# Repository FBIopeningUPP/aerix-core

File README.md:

# AERIX Core

A compact STM32H7 flight controller module.

## Hardware

- STM32H743IIKx
- IIM-42653, ICM-45686, and BMI088 IMUs
- BMP390 and ICP-20100 barometers
- W25Q128JV SPI flash
- microSD card
- Two CAN transceivers
- Buck converter and three 3.3 V LDOs
- SWD and two status LEDs
- Two board-to-board connectors

This board is still being tested and is not ready for flight.

## Board views

## Bring-up

1. Open the [KiCad project](hardware/core/core.kicad_pro).
2. Run ERC and DRC.
3. Check the board for shorts.
4. Power it from a current-limited 3.3 V supply.
5. Connect `VTREF`, `GND`, `SWDIO`, `SWCLK`, and `RESET`.
6. Flash the LED test from the [firmware guide](firmware/README.md).
7. Test storage, sensors, and CAN separately.

## Files

- [Main schematic](hardware/core/core.kicad_sch)
- [MCU schematic](hardware/core/mcu.kicad_sch)
- [Sensor schematic](hardware/core/sensor.kicad_sch)
- [Power schematic](hardware/core/power.kicad_sch)
- [PCB layout](hardware/core/core.kicad_pcb)
- [Symbols, footprints, and 3D models](lib/)
- [Production files](hardware/core/production/)

## Production

- [Bill of materials](hardware/core/production/bom.csv)
- [Component positions](hardware/core/production/positions.csv)
- [Designators](hardware/core/production/designators.csv)
- [IPC netlist](hardware/core/production/netlist.ipc)

The BOM contains 25 line items and 91 parts.

| Designator | Footprint | Qty | Value | Source |
| --- | --- | ---: | --- | --- |
| C1, C2-C15, C20, C22, C24, C27, C28, C30, C31, C33-C38, C40, C41, C43, C44, C46-C48 | 0201 | 35 | 100nF | [LCSC search](https://www.lcsc.com/search?q=0201%20100nF) |
| C16-C18 | 0201 | 3 | 4.7uF | [LCSC search](https://www.lcsc.com/search?q=0201%204.7uF) |
| C19, C21, C23, C51-C56 | 0402 | 9 | 1uF | [LCSC search](https://www.lcsc.com/search?q=0402%201uF) |
| C25, C26, C29, C32 | 0402 | 4 | 2.2uF | [LCSC search](https://www.lcsc.com/search?q=0402%202.2uF) |
| C42, C45 | 0402 | 2 | 4.7uF | [LCSC search](https://www.lcsc.com/search?q=0402%204.7uF) |
| C49 | 0603 | 1 | 10uF | [LCSC search](https://www.lcsc.com/search?q=0603%2010uF) |
| C50 | 0603 | 1 | 22uF | [LCSC search](https://www.lcsc.com/search?q=0603%2022uF) |
| CARD1 | TF-SMD_TF-021B-H265 | 1 | TF-021B-H265 | [C498185](https://www.lcsc.com/product-detail/C498185.html) |
| CN1, CN2 | CONN-SMD_DF40C-80DS-0.4V-51 | 2 | DF40C-80DS-0.4V | [C312960](https://www.lcsc.com/product-detail/C312960.html) |
| FB1-FB3 | 0603 | 3 | 600R | [LCSC search](https://www.lcsc.com/search?q=0603%20600R%20ferrite%20bead) |
| LED1, LED2 | 0402 | 2 | LED | [LCSC search](https://www.lcsc.com/search?q=0402%20LED) |
| R1-R7 | 0201 | 7 | 10k | [LCSC search](https://www.lcsc.com/search?q=0201%2010k) |
| R8-R12 | 0201 | 5 | 47k | [LCSC search](https://www.lcsc.com/search?q=0201%2047k) |
| R13, R14 | 0201 | 2 | 1k | [LCSC search](https://www.lcsc.com/search?q=0201%201k) |
| U1 | UFBGA-201 | 1 | STM32H743IIKx | [LCSC search](https://www.lcsc.com/search?q=STM32H743IIKx) |
| U9, U10 | TDFN-8 | 2 | TCAN1044AVDRBRQ1 | [C3234119](https://www.lcsc.com/product-detail/C3234119.html) |
| U11-U13 | X2SON-4 | 3 | TPS7A2033PDQNR | [C2871641](https://www.lcsc.com/product-detail/C2871641.html) |
| U14 | USIP-10 | 1 | TPSM82822SILR | [C5219367](https://www.lcsc.com/product-detail/C5219367.html) |
| U2 | LGA-14 | 1 | IIM-42653 | [C30724128](https://www.lcsc.com/product-detail/C30724128.html) |
| U3 | LGA-14 | 1 | ICM-45686 | [C22459454](https://www.lcsc.com/product-detail/C22459454.html) |
| U4 | LGA-16 | 1 | BMI088 | [C194919](https://www.lcsc.com/product-detail/C194919.html) |
| U5 | LGA-10 | 1 | BMP390 | [C5124834](https://www.lcsc.com/product-detail/C5124834.html) |
| U6 | LGA-10 | 1 | ICP-20100 | [C5343527](https://www.lcsc.com/product-detail/C5343527.html) |
| U7 | WSON-8 | 1 | W25Q128JVE | [LCSC search](https://www.lcsc.com/search?q=W25Q128JVE) |
| X1 | 3.2 × 2.5 mm crystal | 1 | ABM8W-16.0000MHZ-8-D1X-T3 | [C193746](https://www.lcsc.com/product-detail/C193746.html) |

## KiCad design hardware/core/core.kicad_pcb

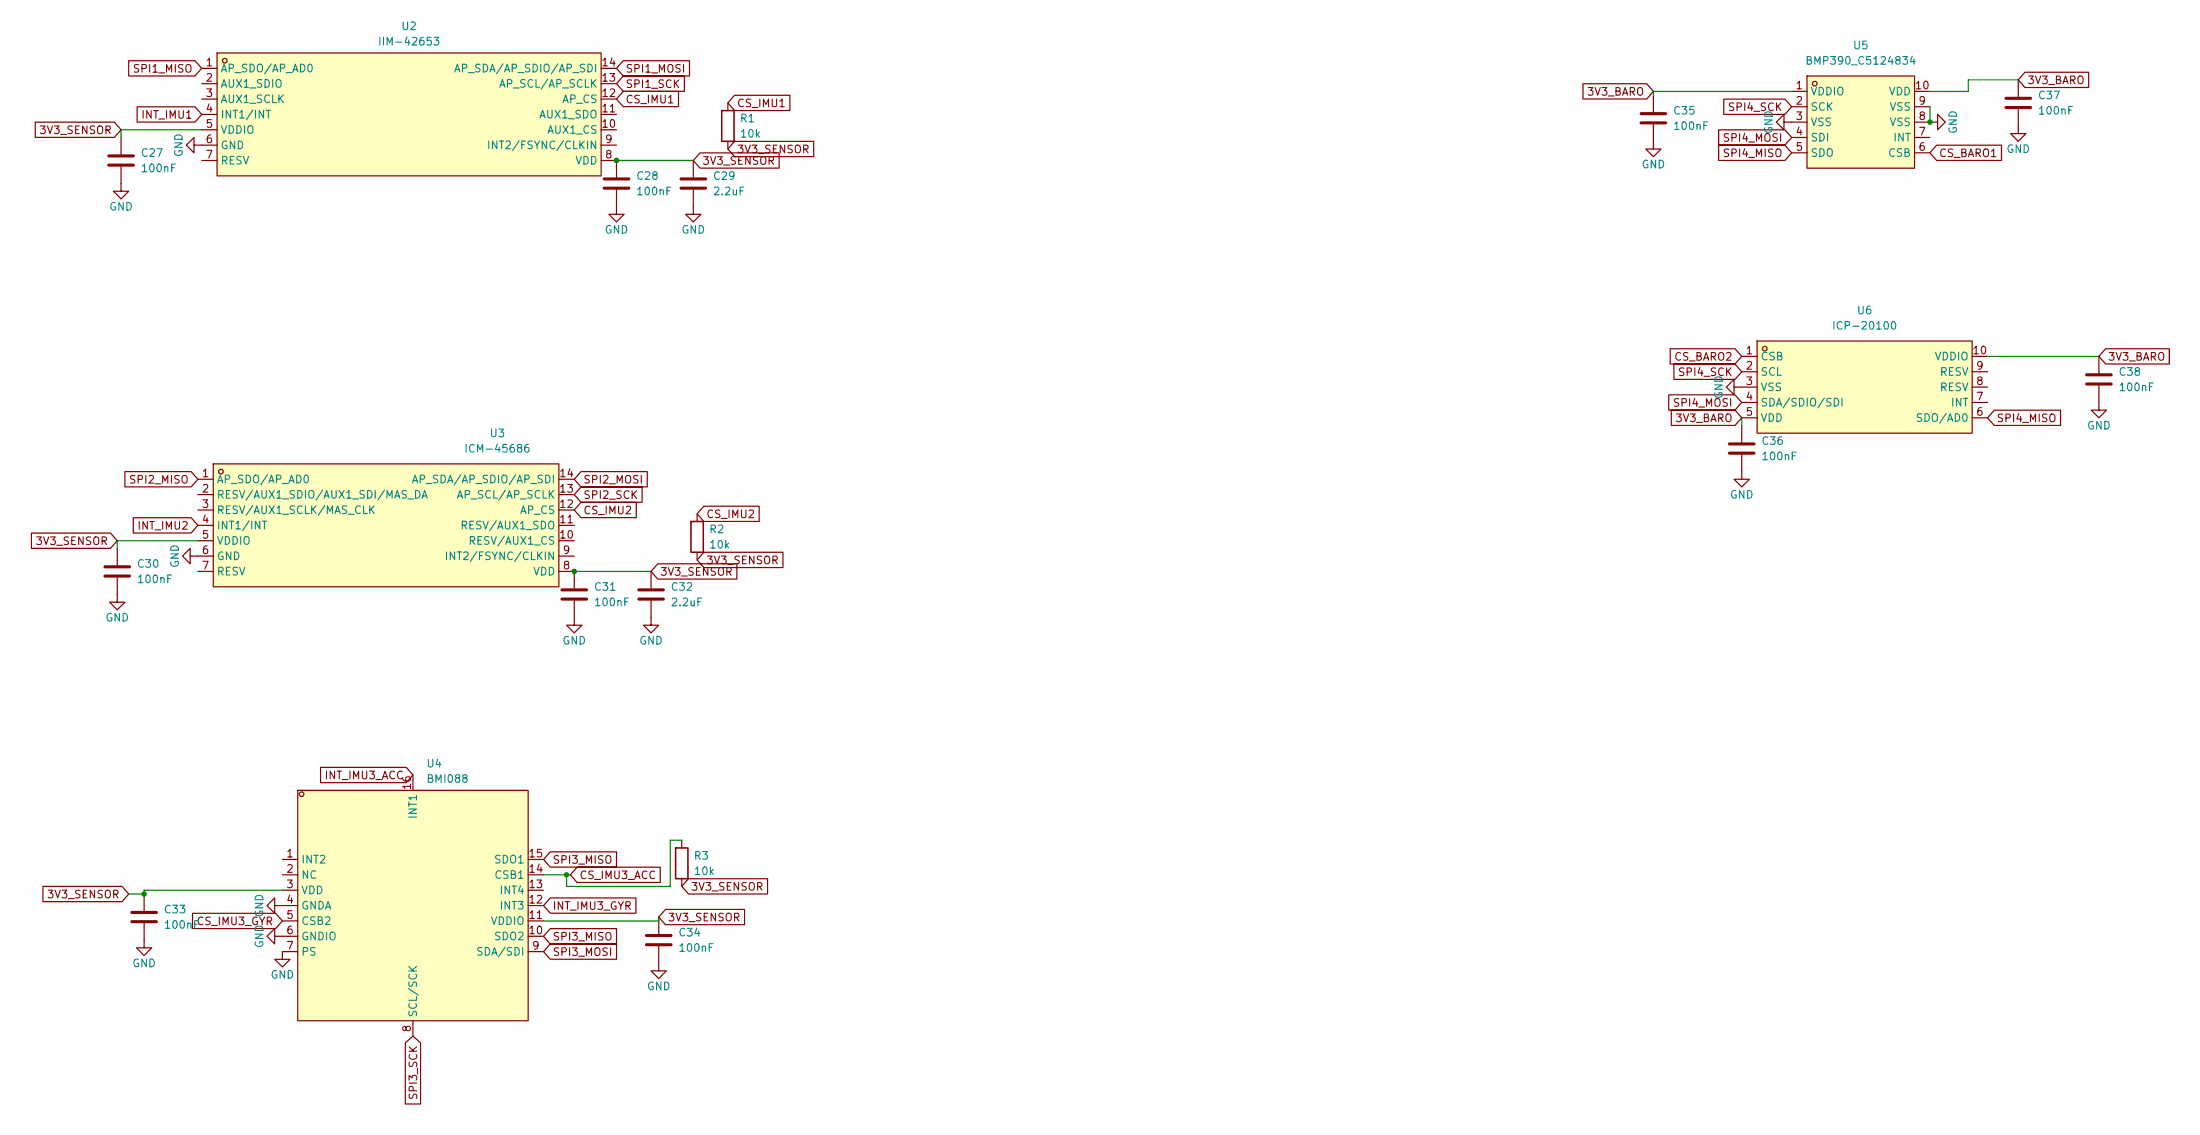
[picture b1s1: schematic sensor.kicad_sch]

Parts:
C27, C28, C30, C31, C33, C34, C35, C36, C37, C38: 100nF; C_0201_0603Metric
C29, C32: 2.2uF; C_0402_1005Metric
R1, R2, R3: 10k; R_0201_0603Metric
U2: IIM-42653; LGA-14_L3.0-W2.5-P0.50-TL; MPN IIM-42653; LCSC Part C30724128
U3: ICM-45686; LGA-14_L3.0-W2.5-P0.50-TL; MPN ICM-45686; LCSC Part C22459454
U4: BMI088; LGA-16_L4.5-W3.0-P0.50-BL; MPN BMI088; LCSC Part C194919
U5: BMP390_C5124834; LGA-10_L2.0-W2.0-P0.50-BL; MPN BMP390; LCSC Part C5124834
U6: ICP-20100; LGA-10_L2.0-W2.0-P0.50-TL_ICP-20100; MPN ICP-20100; LCSC Part C5343527

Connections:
3V3_BARO: C35.1, C36.1, C37.1, C38.1, U5.1 (VDDIO), U5.10 (VDD), U6.5 (VDD), U6.10 (VDDIO); also elsewhere on the board
3V3_SENSOR: C27.1, C28.1, C29.1, C30.1, C31.1, C32.1, C33.1, C34.1, R1.2, R2.2, R3.2, U2.5 (VDDIO), U2.8 (VDD), U3.5 (VDDIO), U3.8 (VDD), U4.3 (VDD), U4.11 (VDDIO); also elsewhere on the board
CS_BARO1: U5.6 (CSB); also elsewhere on the board
CS_BARO2: U6.1 (CSB); also elsewhere on the board
CS_IMU1: R1.1, U2.12 (AP_CS); also elsewhere on the board
CS_IMU2: R2.1, U3.12 (AP_CS); also elsewhere on the board
CS_IMU3_ACC: R3.1, U4.14 (CSB1); also elsewhere on the board
CS_IMU3_GYR: U4.5 (CSB2); also elsewhere on the board
GND: C27.2, C28.2, C29.2, C30.2, C31.2, C32.2, C33.2, C34.2, C35.2, C36.2, C37.2, C38.2, U2.6 (GND), U3.6 (GND), U4.4 (GNDA), U4.6 (GNDIO), U4.7 (PS), U5.3 (VSS), U5.8 (VSS), U5.9 (VSS), U6.3 (VSS); also elsewhere on the board
INT_IMU1: U2.4 (INT1/INT); also elsewhere on the board
INT_IMU2: U3.4 (INT1/INT); also elsewhere on the board
INT_IMU3_ACC: U4.16 (INT1); also elsewhere on the board
INT_IMU3_GYR: U4.12 (INT3); also elsewhere on the board
SPI1_MISO: U2.1 (AP_SDO/AP_AD0); also elsewhere on the board
SPI1_MOSI: U2.14 (AP_SDA/AP_SDIO/AP_SDI); also elsewhere on the board
SPI1_SCK: U2.13 (AP_SCL/AP_SCLK); also elsewhere on the board
SPI2_MISO: U3.1 (AP_SDO/AP_AD0); also elsewhere on the board
SPI2_MOSI: U3.14 (AP_SDA/AP_SDIO/AP_SDI); also elsewhere on the board
SPI2_SCK: U3.13 (AP_SCL/AP_SCLK); also elsewhere on the board
SPI3_MISO: U4.10 (SDO2), U4.15 (SDO1); also elsewhere on the board
SPI3_MOSI: U4.9 (SDA/SDI); also elsewhere on the board
SPI3_SCK: U4.8 (SCL/SCK); also elsewhere on the board
SPI4_MISO: U5.5 (SDO), U6.6 (SDO/AD0); also elsewhere on the board
SPI4_MOSI: U5.4 (SDI), U6.4 (SDA/SDIO/SDI); also elsewhere on the board
SPI4_SCK: U5.2 (SCK), U6.2 (SCL); also elsewhere on the board

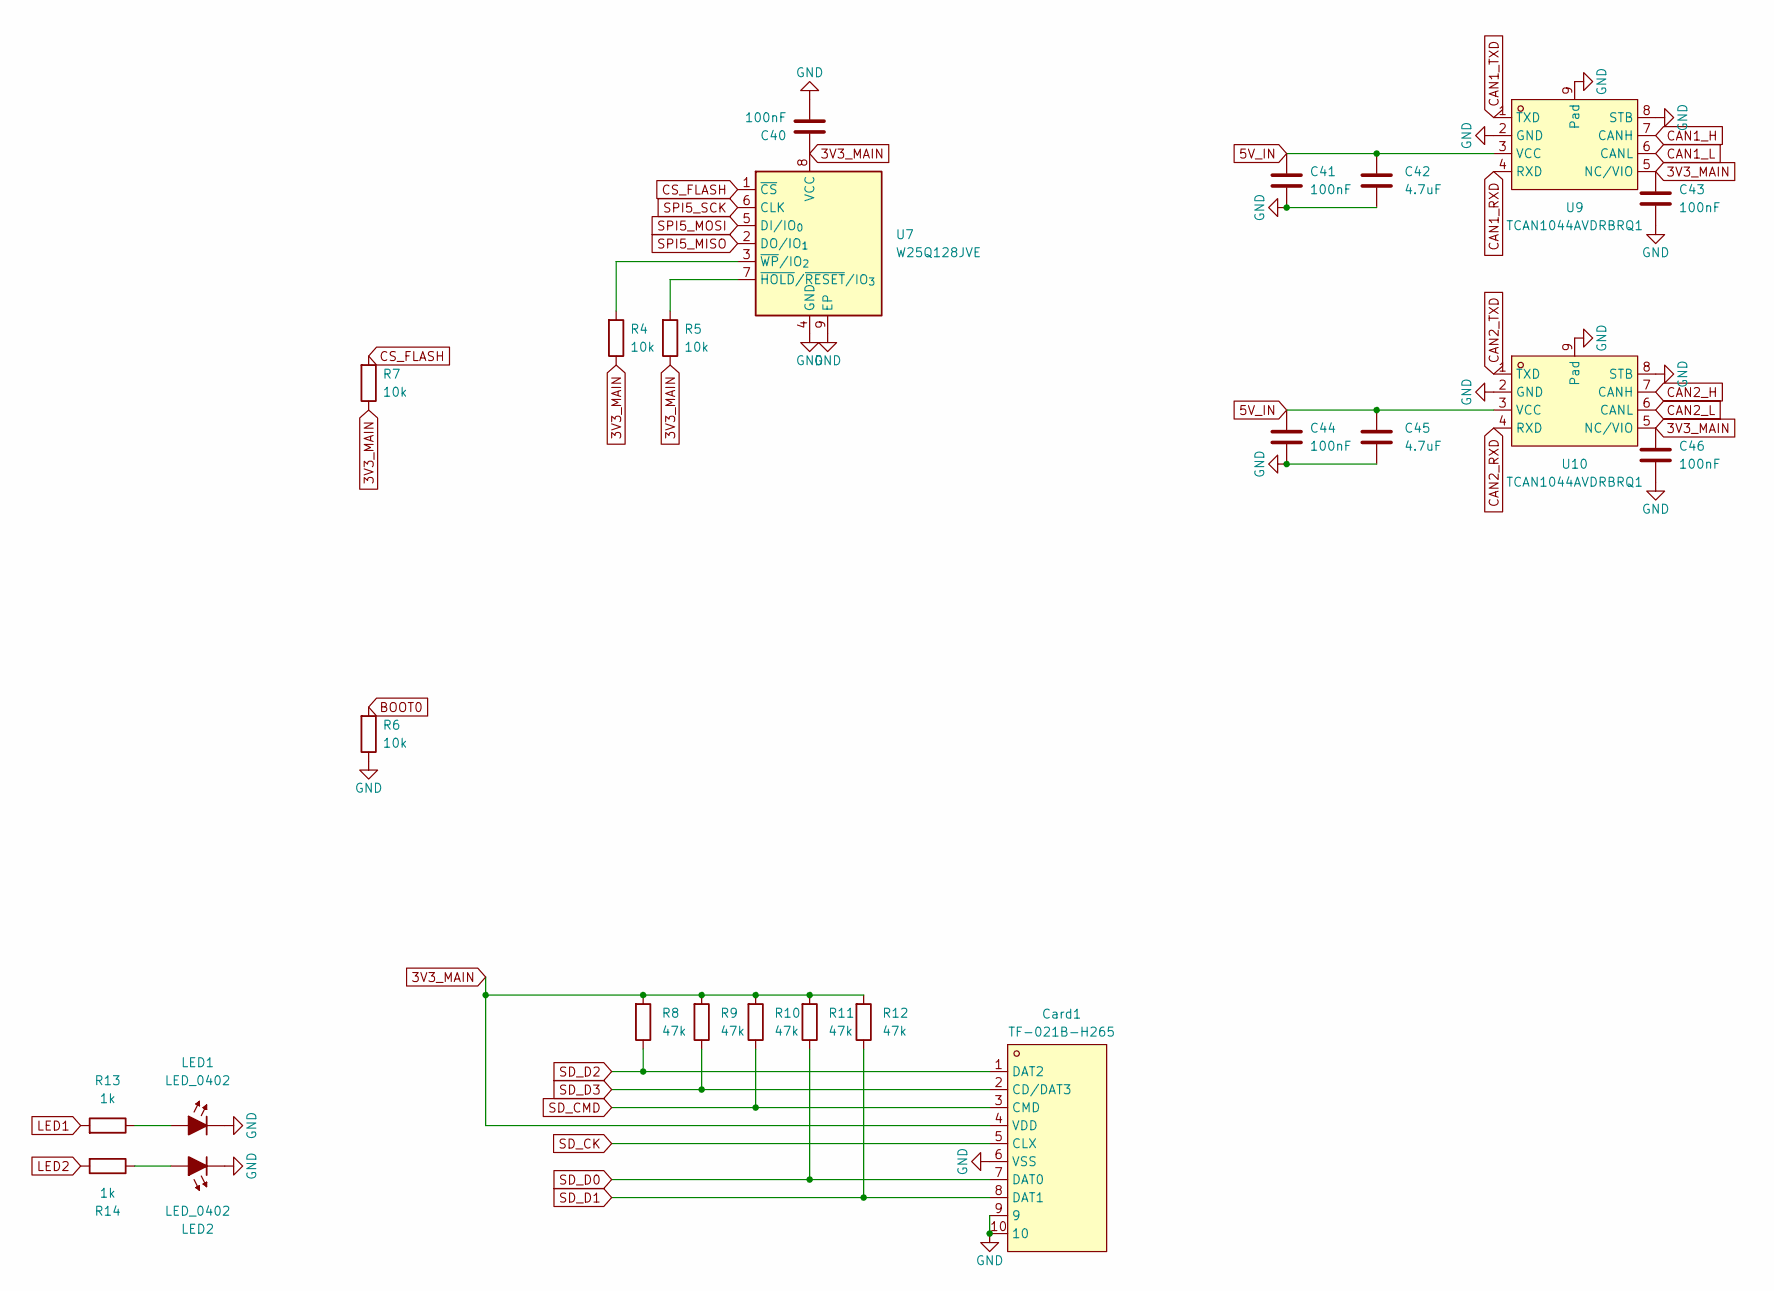
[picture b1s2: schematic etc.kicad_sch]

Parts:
C40, C41, C43, C44, C46: 100nF; C_0201_0603Metric
C42, C45: 4.7uF; C_0402_1005Metric
Card1: TF-021B-H265; TF-SMD_TF-021B-H265; MPN TF-021B-H265; LCSC Part C498185
LED1, LED2: LED_0402; LED_0402_1005Metric
R4, R5, R6, R7: 10k; R_0201_0603Metric
R8, R9, R10, R11, R12: 47k; R_0201_0603Metric
R13, R14: 1k; R_0201_0603Metric
U7: W25Q128JVE; WSON-8-1EP_8x6mm_P1.27mm_EP3.4x4.3mm
U9, U10: TCAN1044AVDRBRQ1; TDFN-8_L3.0-W3.0-P0.65-BL-EP; MPN TCAN1044AVDRBRQ1; LCSC Part C3234119

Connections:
3V3_MAIN: C40.1, C43.1, C46.1, Card1.4 (VDD), R4.2, R5.2, R7.2, R8.1, R9.1, R10.1, R11.1, R12.1, U7.8 (VCC), U9.5 (NC/VIO), U10.5 (NC/VIO); also elsewhere on the board
5V_IN: C41.1, C42.1, C44.1, C45.1, U9.3 (VCC), U10.3 (VCC); also elsewhere on the board
BOOT0: R6.1; also elsewhere on the board
CAN1_H: U9.7 (CANH); also elsewhere on the board
CAN1_L: U9.6 (CANL); also elsewhere on the board
CAN1_RXD: U9.4 (RXD); also elsewhere on the board
CAN1_TXD: U9.1 (TXD); also elsewhere on the board
CAN2_H: U10.7 (CANH); also elsewhere on the board
CAN2_L: U10.6 (CANL); also elsewhere on the board
CAN2_RXD: U10.4 (RXD); also elsewhere on the board
CAN2_TXD: U10.1 (TXD); also elsewhere on the board
CS_FLASH: R7.1, U7.1 (~CS); also elsewhere on the board
GND: C40.2, C41.2, C42.2, C43.2, C44.2, C45.2, C46.2, Card1.6 (VSS), Card1.9, Card1.10, LED1.1 (K), LED2.1 (K), R6.2, U7.4 (GND), U7.9 (EP), U9.2 (GND), U9.8 (STB), U9.9 (Pad), U10.2 (GND), U10.8 (STB), U10.9 (Pad); also elsewhere on the board
LED1: R13.1; also elsewhere on the board
LED2: R14.1; also elsewhere on the board
unnamed: LED1.2 (A), R13.2
unnamed: LED2.2 (A), R14.2
unnamed: R5.1, U7.7 (~HOLD/~RESET/IO_{3})
unnamed: R4.1, U7.3 (~WP/IO_{2})
SD_CK: Card1.5 (CLX); also elsewhere on the board
SD_CMD: Card1.3 (CMD), R10.2; also elsewhere on the board
SD_D0: Card1.7 (DAT0), R11.2; also elsewhere on the board
SD_D1: Card1.8 (DAT1), R12.2; also elsewhere on the board
SD_D2: Card1.1 (DAT2), R8.2; also elsewhere on the board
SD_D3: Card1.2 (CD/DAT3), R9.2; also elsewhere on the board
SPI5_MISO: U7.2 (DO/IO_{1}); also elsewhere on the board
SPI5_MOSI: U7.5 (DI/IO_{0}); also elsewhere on the board
SPI5_SCK: U7.6 (CLK); also elsewhere on the board

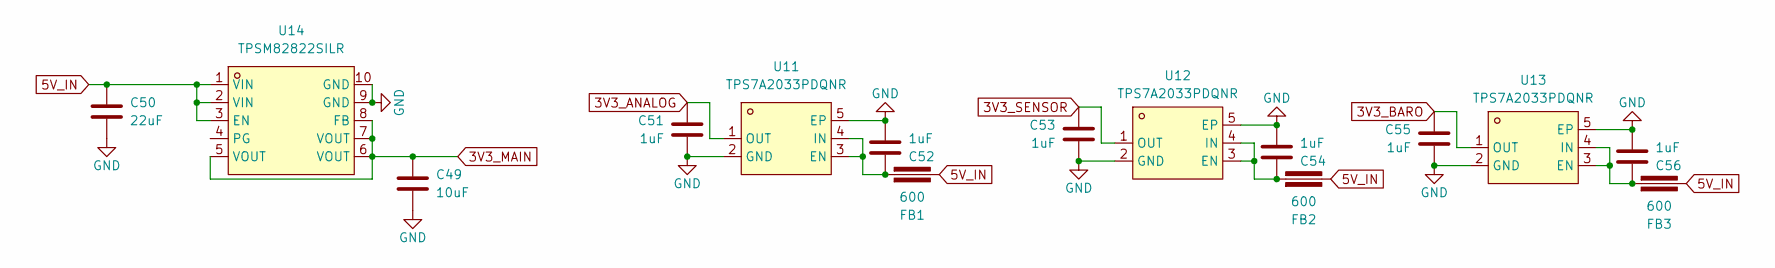
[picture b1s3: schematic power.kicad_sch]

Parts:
C49: 10uF; C_0603_1608Metric
C50: 22uF; C_0603_1608Metric
C51, C52, C53, C54, C55, C56: 1uF; C_0402_1005Metric
FB1, FB2, FB3: 600; Fuse_0603_1608Metric
U11, U12, U13: TPS7A2033PDQNR; X2SON-4_L1.0-W1.0-P0.65-TL-EP; MPN TPS7A2033PDQNR; LCSC Part C2871641
U14: TPSM82822SILR; USIP-10_L2.5-W2.0-P0.50-BL; MPN TPSM82822SILR; LCSC Part C5219367

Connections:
3V3_ANALOG: C51.2, U11.1 (OUT); also elsewhere on the board
3V3_BARO: C55.2, U13.1 (OUT); also elsewhere on the board
3V3_MAIN: C49.1, U14.5 (VOUT), U14.6 (VOUT), U14.7 (VOUT), U14.8 (FB); also elsewhere on the board
3V3_SENSOR: C53.2, U12.1 (OUT); also elsewhere on the board
5V_IN: C50.1, FB1.2, FB2.2, FB3.2, U14.1 (VIN), U14.2 (VIN), U14.3 (EN); also elsewhere on the board
GND: C49.2, C50.2, C51.1, C52.1, C53.1, C54.1, C55.1, C56.1, U11.2 (GND), U11.5 (EP), U12.2 (GND), U12.5 (EP), U13.2 (GND), U13.5 (EP), U14.9 (GND), U14.10 (GND); also elsewhere on the board
unnamed: C52.2, FB1.1, U11.3 (EN), U11.4 (IN)
unnamed: C54.2, FB2.1, U12.3 (EN), U12.4 (IN)
unnamed: C56.2, FB3.1, U13.3 (EN), U13.4 (IN)

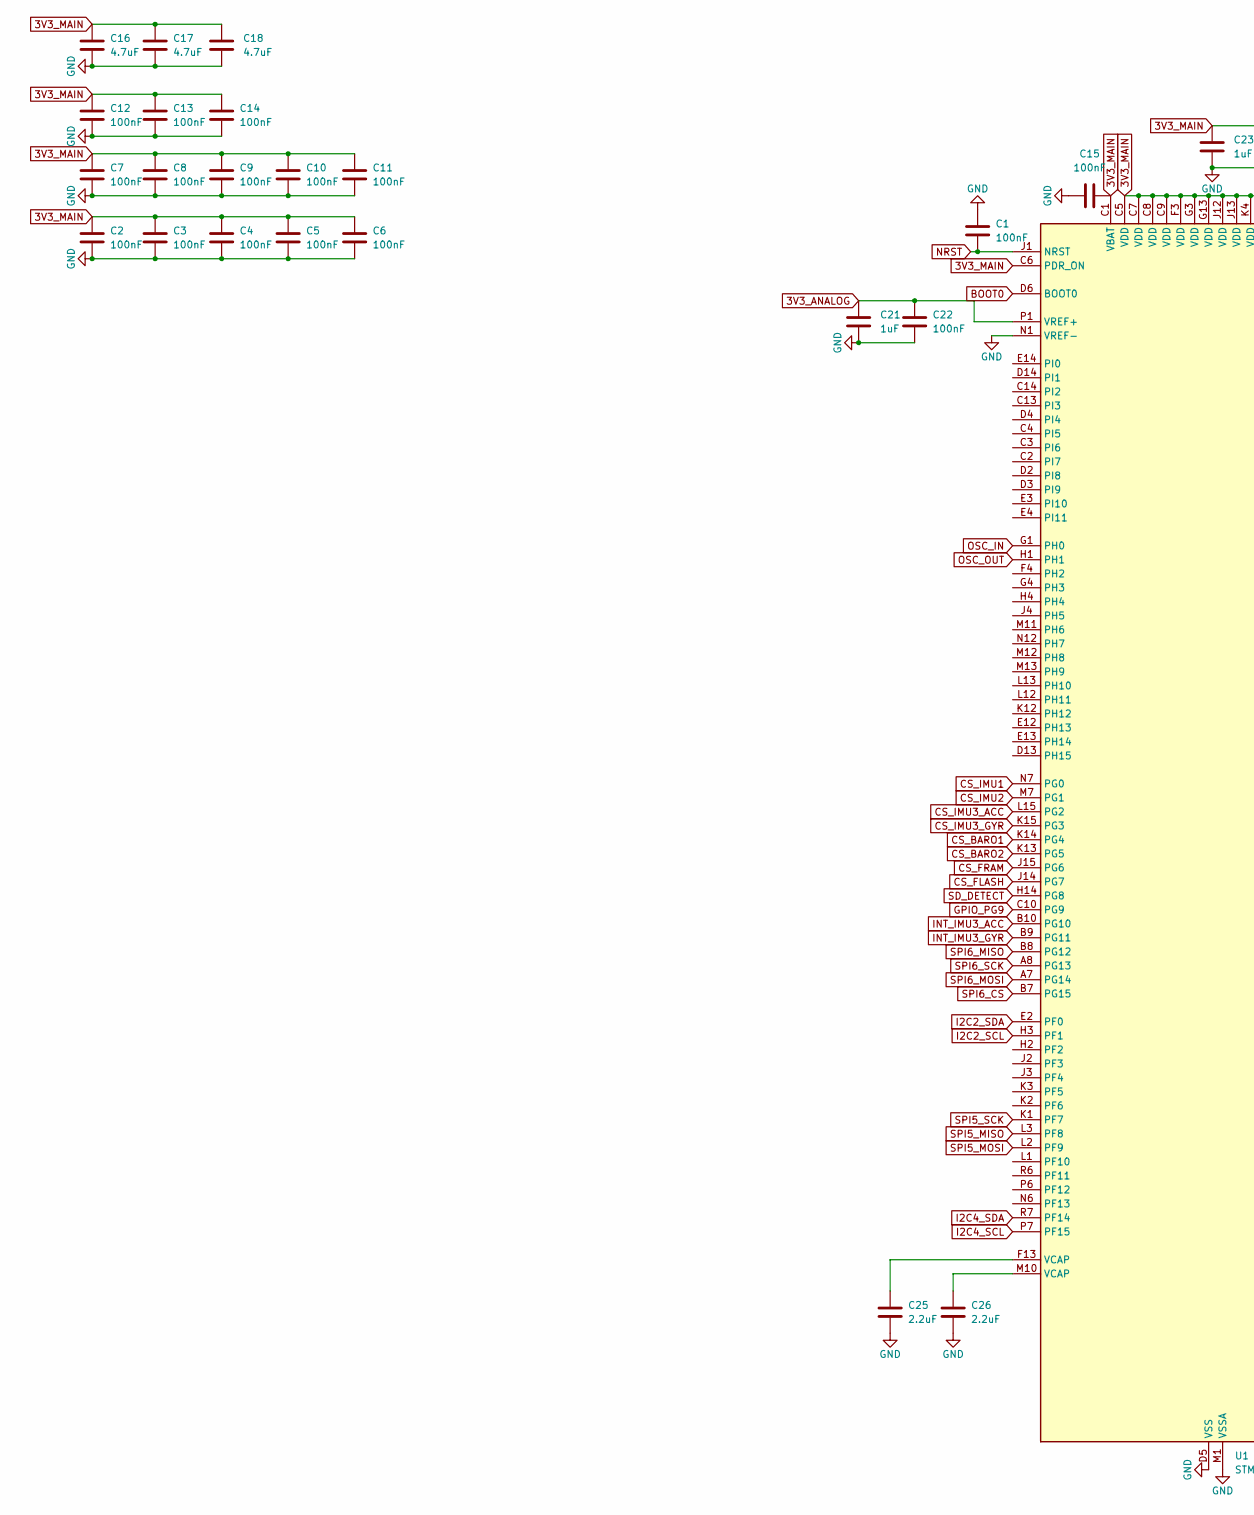
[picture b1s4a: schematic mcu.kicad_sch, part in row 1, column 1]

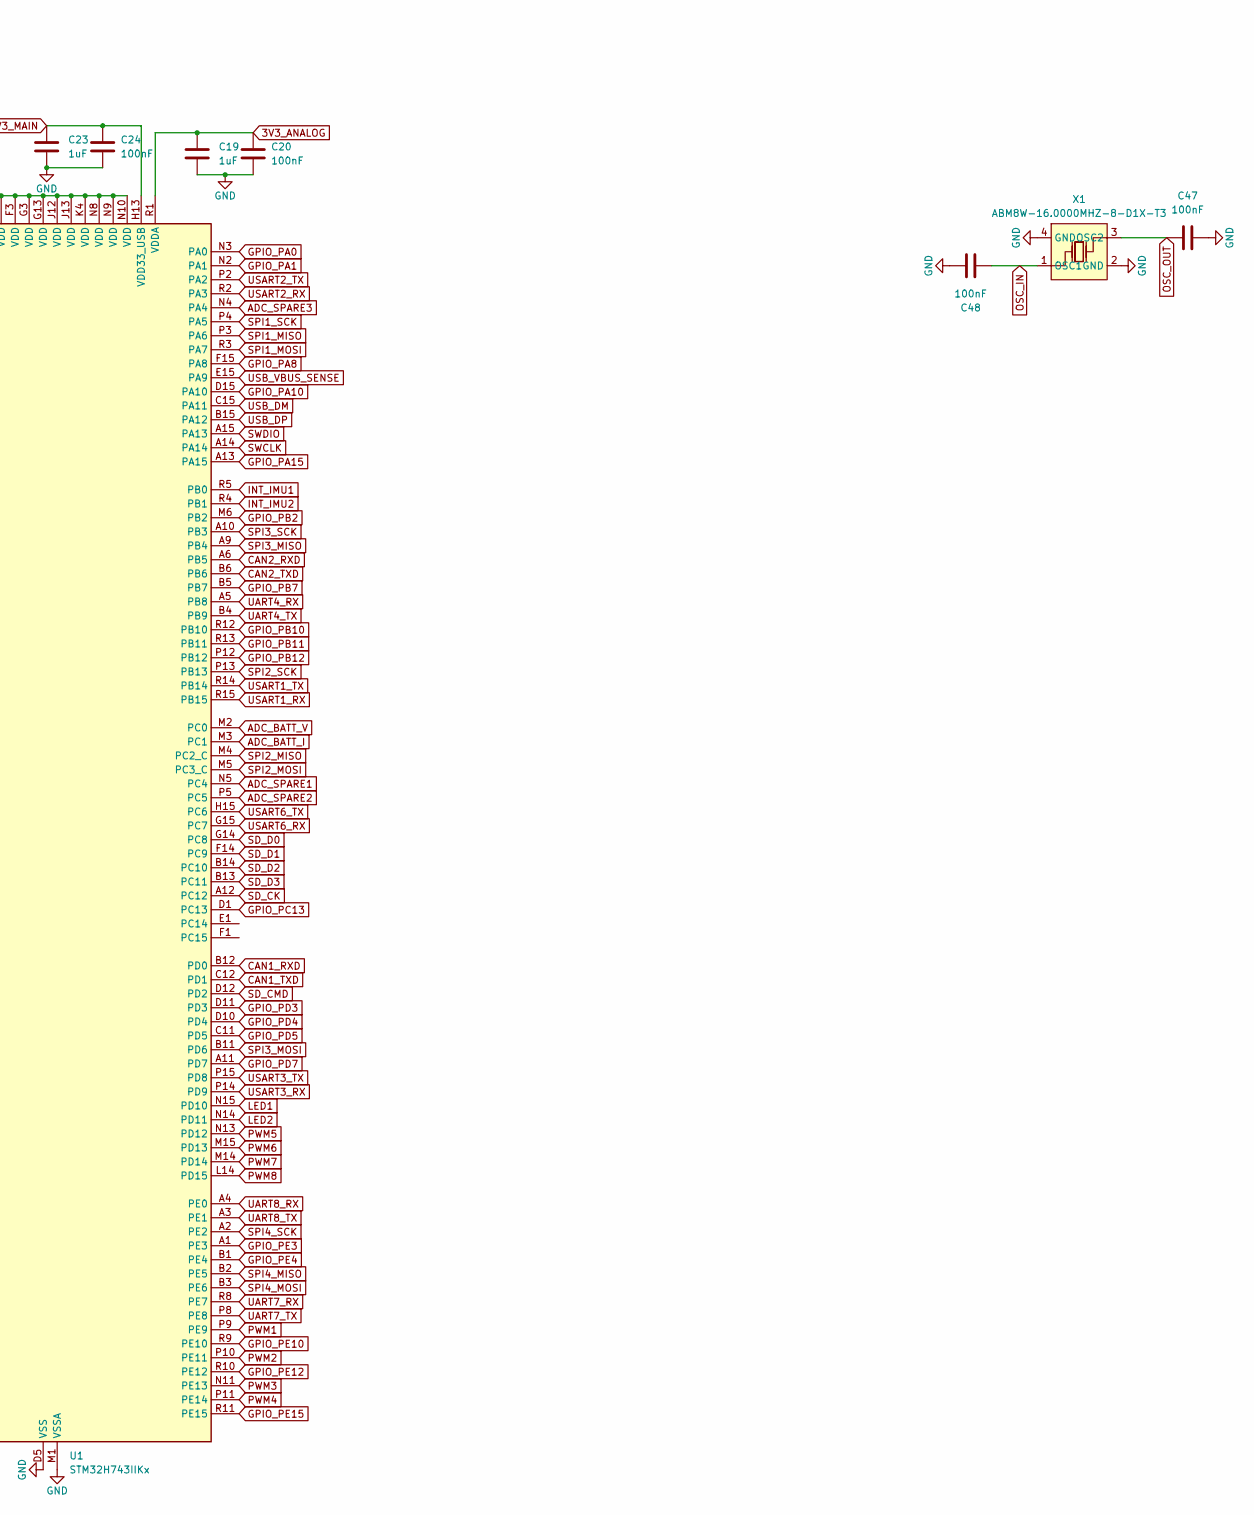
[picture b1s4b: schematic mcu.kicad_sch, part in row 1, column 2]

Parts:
C1, C2, C3, C4, C5, C6, C7, C8, C9, C10, C11, C12, C13, C14, C15, C20, C22, C24, C47, C48: 100nF; C_0201_0603Metric
C16, C17, C18: 4.7uF; C_0201_0603Metric
C19, C21, C23: 1uF; C_0402_1005Metric
C25, C26: 2.2uF; C_0402_1005Metric
U1: STM32H743IIKx; UFBGA-201_10x10mm_Layout15x15_P0.65mm
X1: ABM8W-16.0000MHZ-8-D1X-T3; CRYSTAL-SMD_4P-L3.2-W2.5-BL-1; MPN ABM8W-16.0000MHZ-8-D1X-T3; LCSC Part C193746

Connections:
3V3_ANALOG: C19.1, C20.1, C21.1, C22.1, U1.P1 (VREF+), U1.R1 (VDDA); also elsewhere on the board
3V3_MAIN: C2.1, C3.1, C4.1, C5.1, C6.1, C7.1, C8.1, C9.1, C10.1, C11.1, C12.1, C13.1, C14.1, C15.2, C16.1, C17.1, C18.1, C23.1, C24.1, U1.C1 (VBAT), U1.C5 (VDD), U1.C6 (PDR_ON), U1.C7 (VDD), U1.C8 (VDD), U1.C9 (VDD), U1.F3 (VDD), U1.G3 (VDD), U1.G13 (VDD), U1.H13 (VDD33_USB), U1.J12 (VDD), U1.J13 (VDD), U1.K4 (VDD), U1.N8 (VDD), U1.N9 (VDD), U1.N10 (VDD); also elsewhere on the board
ADC_BATT_I: U1.M3 (PC1); also elsewhere on the board
ADC_BATT_V: U1.M2 (PC0); also elsewhere on the board
ADC_SPARE1: U1.N5 (PC4); also elsewhere on the board
ADC_SPARE2: U1.P5 (PC5); also elsewhere on the board
ADC_SPARE3: U1.N4 (PA4); also elsewhere on the board
BOOT0: U1.D6 (BOOT0); also elsewhere on the board
CAN1_RXD: U1.B12 (PD0); also elsewhere on the board
CAN1_TXD: U1.C12 (PD1); also elsewhere on the board
CAN2_RXD: U1.A6 (PB5); also elsewhere on the board
CAN2_TXD: U1.B6; also elsewhere on the board
CS_BARO1: U1.K14 (PG4); also elsewhere on the board
CS_BARO2: U1.K13 (PG5); also elsewhere on the board
CS_FLASH: U1.J14 (PG7); also elsewhere on the board
CS_FRAM: U1.J15 (PG6)
CS_IMU1: U1.N7 (PG0); also elsewhere on the board
CS_IMU2: U1.M7 (PG1); also elsewhere on the board
CS_IMU3_ACC: U1.L15 (PG2); also elsewhere on the board
CS_IMU3_GYR: U1.K15 (PG3); also elsewhere on the board
GND: C1.1, C2.2, C3.2, C4.2, C5.2, C6.2, C7.2, C8.2, C9.2, C10.2, C11.2, C12.2, C13.2, C14.2, C15.1, C16.2, C17.2, C18.2, C19.2, C20.2, C21.2, C22.2, C23.2, C24.2, C25.2, C26.2, C47.2, C48.2, U1.D5 (VSS), U1.D7 (VSS), U1.D8 (VSS), U1.D9 (VSS), U1.F2 (VSS), U1.F6 (VSS), U1.F7 (VSS), U1.F8 (VSS), U1.F9 (VSS), U1.F10 (VSS), U1.F12 (VSS), U1.G2 (VSS), U1.G6 (VSS), U1.G7 (VSS), U1.G8 (VSS), U1.G9 (VSS), U1.G10 (VSS), U1.G12 (VSS), U1.H6 (VSS), U1.H7 (VSS), U1.H8 (VSS), U1.H9 (VSS), U1.H10 (VSS), U1.H12 (VSS), U1.J6 (VSS), U1.J7 (VSS), U1.J8 (VSS), U1.J9 (VSS), U1.J10 (VSS), U1.K6 (VSS), U1.K7 (VSS), U1.K8 (VSS), U1.K9 (VSS), U1.K10 (VSS), U1.L4 (VSS), U1.M1 (VSSA), U1.M8 (VSS), U1.M9 (VSS), U1.N1 (VREF-), X1.2 (GND), X1.4 (GND); also elsewhere on the board
GPIO_PA0: U1.N3 (PA0); also elsewhere on the board
GPIO_PA1: U1.N2 (PA1); also elsewhere on the board
GPIO_PA8: U1.F15 (PA8); also elsewhere on the board
GPIO_PA10: U1.D15 (PA10); also elsewhere on the board
GPIO_PA15: U1.A13 (PA15); also elsewhere on the board
GPIO_PB2: U1.M6 (PB2); also elsewhere on the board
GPIO_PB7: U1.B5 (PB7); also elsewhere on the board
GPIO_PB10: U1.R12 (PB10); also elsewhere on the board
GPIO_PB11: U1.R13 (PB11); also elsewhere on the board
GPIO_PB12: U1.P12 (PB12); also elsewhere on the board
GPIO_PC13: U1.D1 (PC13); also elsewhere on the board
GPIO_PD3: U1.D11 (PD3); also elsewhere on the board
GPIO_PD4: U1.D10 (PD4); also elsewhere on the board
GPIO_PD5: U1.C11 (PD5); also elsewhere on the board
GPIO_PD7: U1.A11 (PD7); also elsewhere on the board
GPIO_PE3: U1.A1 (PE3); also elsewhere on the board
GPIO_PE4: U1.B1 (PE4); also elsewhere on the board
GPIO_PE10: U1.R9 (PE10); also elsewhere on the board
GPIO_PE12: U1.R10 (PE12); also elsewhere on the board
GPIO_PE15: U1.R11 (PE15); also elsewhere on the board
GPIO_PG9: U1.C10 (PG9); also elsewhere on the board
I2C2_SCL: U1.H3 (PF1); also elsewhere on the board
I2C2_SDA: U1.E2 (PF0); also elsewhere on the board
I2C4_SCL: U1.P7 (PF15); also elsewhere on the board
I2C4_SDA: U1.R7 (PF14); also elsewhere on the board
INT_IMU1: U1.R5 (PB0); also elsewhere on the board
INT_IMU2: U1.R4 (PB1); also elsewhere on the board
INT_IMU3_ACC: U1.B10 (PG10); also elsewhere on the board
INT_IMU3_GYR: U1.B9 (PG11); also elsewhere on the board
LED1: U1.N15 (PD10); also elsewhere on the board
LED2: U1.N14 (PD11); also elsewhere on the board
NRST: C1.2, U1.J1 (NRST); also elsewhere on the board
unnamed: C25.1, U1.F13 (VCAP)
unnamed: C26.1, U1.M10 (VCAP)
OSC_IN: C48.1, U1.G1 (PH0), X1.1 (OSC1)
OSC_OUT: C47.1, U1.H1, X1.3 (OSC2)
PWM1: U1.P9 (PE9); also elsewhere on the board
PWM2: U1.P10 (PE11); also elsewhere on the board
PWM3: U1.N11 (PE13); also elsewhere on the board
PWM4: U1.P11 (PE14); also elsewhere on the board
PWM5: U1.N13 (PD12); also elsewhere on the board
PWM6: U1.M15 (PD13); also elsewhere on the board
PWM7: U1.M14 (PD14); also elsewhere on the board
PWM8: U1.L14 (PD15); also elsewhere on the board
SD_CK: U1.A12 (PC12); also elsewhere on the board
SD_CMD: U1.D12 (PD2); also elsewhere on the board
SD_D0: U1.G14 (PC8); also elsewhere on the board
SD_D1: U1.F14 (PC9); also elsewhere on the board
SD_D2: U1.B14 (PC10); also elsewhere on the board
SD_D3: U1.B13 (PC11); also elsewhere on the board
SD_DETECT: U1.H14 (PG8)
SPI1_MISO: U1.P3 (PA6); also elsewhere on the board
SPI1_MOSI: U1.R3 (PA7); also elsewhere on the board
SPI1_SCK: U1.P4 (PA5); also elsewhere on the board
SPI2_MISO: U1.M4 (PC2_C); also elsewhere on the board
SPI2_MOSI: U1.M5 (PC3_C); also elsewhere on the board
SPI2_SCK: U1.P13 (PB13); also elsewhere on the board
SPI3_MISO: U1.A9 (PB4); also elsewhere on the board
SPI3_MOSI: U1.B11 (PD6); also elsewhere on the board
SPI3_SCK: U1.A10 (PB3); also elsewhere on the board
SPI4_MISO: U1.B2 (PE5); also elsewhere on the board
SPI4_MOSI: U1.B3 (PE6); also elsewhere on the board
SPI4_SCK: U1.A2 (PE2); also elsewhere on the board
SPI5_MISO: U1.L3 (PF8); also elsewhere on the board
SPI5_MOSI: U1.L2 (PF9); also elsewhere on the board
SPI5_SCK: U1.K1 (PF7); also elsewhere on the board
SPI6_CS: U1.B7 (PG15); also elsewhere on the board
SPI6_MISO: U1.B8 (PG12); also elsewhere on the board
SPI6_MOSI: U1.A7 (PG14); also elsewhere on the board
SPI6_SCK: U1.A8 (PG13); also elsewhere on the board
SWCLK: U1.A14; also elsewhere on the board
SWDIO: U1.A15 (PA13); also elsewhere on the board
UART4_RX: U1.A5 (PB8); also elsewhere on the board
UART4_TX: U1.B4 (PB9); also elsewhere on the board
UART7_RX: U1.R8 (PE7); also elsewhere on the board
UART7_TX: U1.P8 (PE8); also elsewhere on the board
UART8_RX: U1.A4 (PE0); also elsewhere on the board
UART8_TX: U1.A3 (PE1); also elsewhere on the board
USART1_RX: U1.R15 (PB15); also elsewhere on the board
USART1_TX: U1.R14 (PB14); also elsewhere on the board
USART2_RX: U1.R2 (PA3); also elsewhere on the board
USART2_TX: U1.P2 (PA2); also elsewhere on the board
USART3_RX: U1.P14 (PD9); also elsewhere on the board
USART3_TX: U1.P15 (PD8); also elsewhere on the board
USART6_RX: U1.G15 (PC7); also elsewhere on the board
USART6_TX: U1.H15 (PC6); also elsewhere on the board
USB_DM: U1.C15 (PA11); also elsewhere on the board
USB_DP: U1.B15 (PA12); also elsewhere on the board
USB_VBUS_SENSE: U1.E15 (PA9); also elsewhere on the board

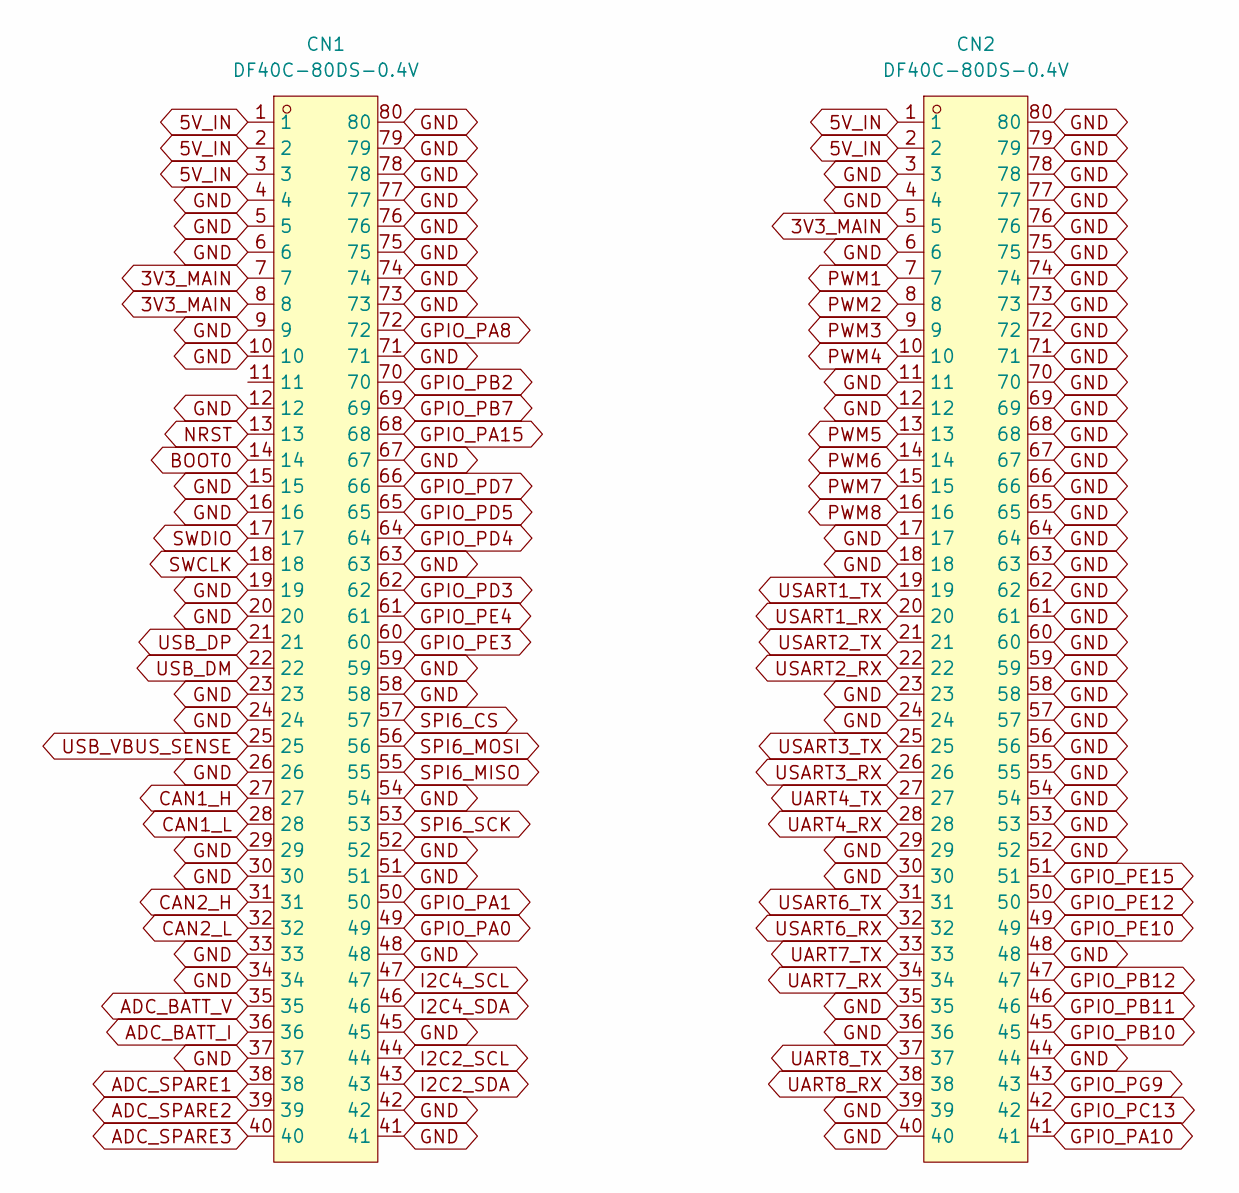
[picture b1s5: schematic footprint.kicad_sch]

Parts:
CN1, CN2: DF40C-80DS-0.4V; CONN-SMD_DF40C-80DS-0.4V-51; MPN DF40C-80DS-0.4V(51); LCSC Part C312960

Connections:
3V3_MAIN: CN1.7, CN1.8, CN2.5; also elsewhere on the board
5V_IN: CN1.1, CN1.2, CN1.3, CN2.1, CN2.2; also elsewhere on the board
ADC_BATT_I: CN1.36; also elsewhere on the board
ADC_BATT_V: CN1.35; also elsewhere on the board
ADC_SPARE1: CN1.38; also elsewhere on the board
ADC_SPARE2: CN1.39; also elsewhere on the board
ADC_SPARE3: CN1.40; also elsewhere on the board
BOOT0: CN1.14; also elsewhere on the board
CAN1_H: CN1.27; also elsewhere on the board
CAN1_L: CN1.28; also elsewhere on the board
CAN2_H: CN1.31; also elsewhere on the board
CAN2_L: CN1.32; also elsewhere on the board
GND: CN1.4, CN1.5, CN1.6, CN1.9, CN1.10, CN1.12, CN1.15, CN1.16, CN1.19, CN1.20, CN1.23, CN1.24, CN1.26, CN1.29, CN1.30, CN1.33, CN1.34, CN1.37, CN1.41, CN1.42, CN1.45, CN1.48, CN1.51, CN1.52, CN1.54, CN1.58, CN1.59, CN1.63, CN1.67, CN1.71, CN1.73, CN1.74, CN1.75, CN1.76, CN1.77, CN1.78, CN1.79, CN1.80, CN2.3, CN2.4, CN2.6, CN2.11, CN2.12, CN2.17, CN2.18, CN2.23, CN2.24, CN2.29, CN2.30, CN2.35, CN2.36, CN2.39, CN2.40, CN2.44, CN2.48, CN2.52, CN2.53, CN2.54, CN2.55, CN2.56, CN2.57, CN2.58, CN2.59, CN2.60, CN2.61, CN2.62, CN2.63, CN2.64, CN2.65, CN2.66, CN2.67, CN2.68, CN2.69, CN2.70, CN2.71, CN2.72, CN2.73, CN2.74, CN2.75, CN2.76, CN2.77, CN2.78, CN2.79, CN2.80; also elsewhere on the board
GPIO_PA0: CN1.49; also elsewhere on the board
GPIO_PA1: CN1.50; also elsewhere on the board
GPIO_PA8: CN1.72; also elsewhere on the board
GPIO_PA10: CN2.41; also elsewhere on the board
GPIO_PA15: CN1.68; also elsewhere on the board
GPIO_PB2: CN1.70; also elsewhere on the board
GPIO_PB7: CN1.69; also elsewhere on the board
GPIO_PB10: CN2.45; also elsewhere on the board
GPIO_PB11: CN2.46; also elsewhere on the board
GPIO_PB12: CN2.47; also elsewhere on the board
GPIO_PC13: CN2.42; also elsewhere on the board
GPIO_PD3: CN1.62; also elsewhere on the board
GPIO_PD4: CN1.64; also elsewhere on the board
GPIO_PD5: CN1.65; also elsewhere on the board
GPIO_PD7: CN1.66; also elsewhere on the board
GPIO_PE3: CN1.60; also elsewhere on the board
GPIO_PE4: CN1.61; also elsewhere on the board
GPIO_PE10: CN2.49; also elsewhere on the board
GPIO_PE12: CN2.50; also elsewhere on the board
GPIO_PE15: CN2.51; also elsewhere on the board
GPIO_PG9: CN2.43; also elsewhere on the board
I2C2_SCL: CN1.44; also elsewhere on the board
I2C2_SDA: CN1.43; also elsewhere on the board
I2C4_SCL: CN1.47; also elsewhere on the board
I2C4_SDA: CN1.46; also elsewhere on the board
NRST: CN1.13; also elsewhere on the board
PWM1: CN2.7; also elsewhere on the board
PWM2: CN2.8; also elsewhere on the board
PWM3: CN2.9; also elsewhere on the board
PWM4: CN2.10; also elsewhere on the board
PWM5: CN2.13; also elsewhere on the board
PWM6: CN2.14; also elsewhere on the board
PWM7: CN2.15; also elsewhere on the board
PWM8: CN2.16; also elsewhere on the board
SPI6_CS: CN1.57; also elsewhere on the board
SPI6_MISO: CN1.55; also elsewhere on the board
SPI6_MOSI: CN1.56; also elsewhere on the board
SPI6_SCK: CN1.53; also elsewhere on the board
SWCLK: CN1.18; also elsewhere on the board
SWDIO: CN1.17; also elsewhere on the board
UART4_RX: CN2.28; also elsewhere on the board
UART4_TX: CN2.27; also elsewhere on the board
UART7_RX: CN2.34; also elsewhere on the board
UART7_TX: CN2.33; also elsewhere on the board
UART8_RX: CN2.38; also elsewhere on the board
UART8_TX: CN2.37; also elsewhere on the board
USART1_RX: CN2.20; also elsewhere on the board
USART1_TX: CN2.19; also elsewhere on the board
USART2_RX: CN2.22; also elsewhere on the board
USART2_TX: CN2.21; also elsewhere on the board
USART3_RX: CN2.26; also elsewhere on the board
USART3_TX: CN2.25; also elsewhere on the board
USART6_RX: CN2.32; also elsewhere on the board
USART6_TX: CN2.31; also elsewhere on the board
USB_DM: CN1.22; also elsewhere on the board
USB_DP: CN1.21; also elsewhere on the board
USB_VBUS_SENSE: CN1.25; also elsewhere on the board
